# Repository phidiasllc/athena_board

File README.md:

The Athena Board is a 3-D printer controller board designed to interface with the Orange Pi Zero.

Note pin mappings can differ based upon the definition used by the firmware developer. The pin mapping shown in the spreadsheet is based on the mighty1284p definition; Sanguinololu uses different definitions.

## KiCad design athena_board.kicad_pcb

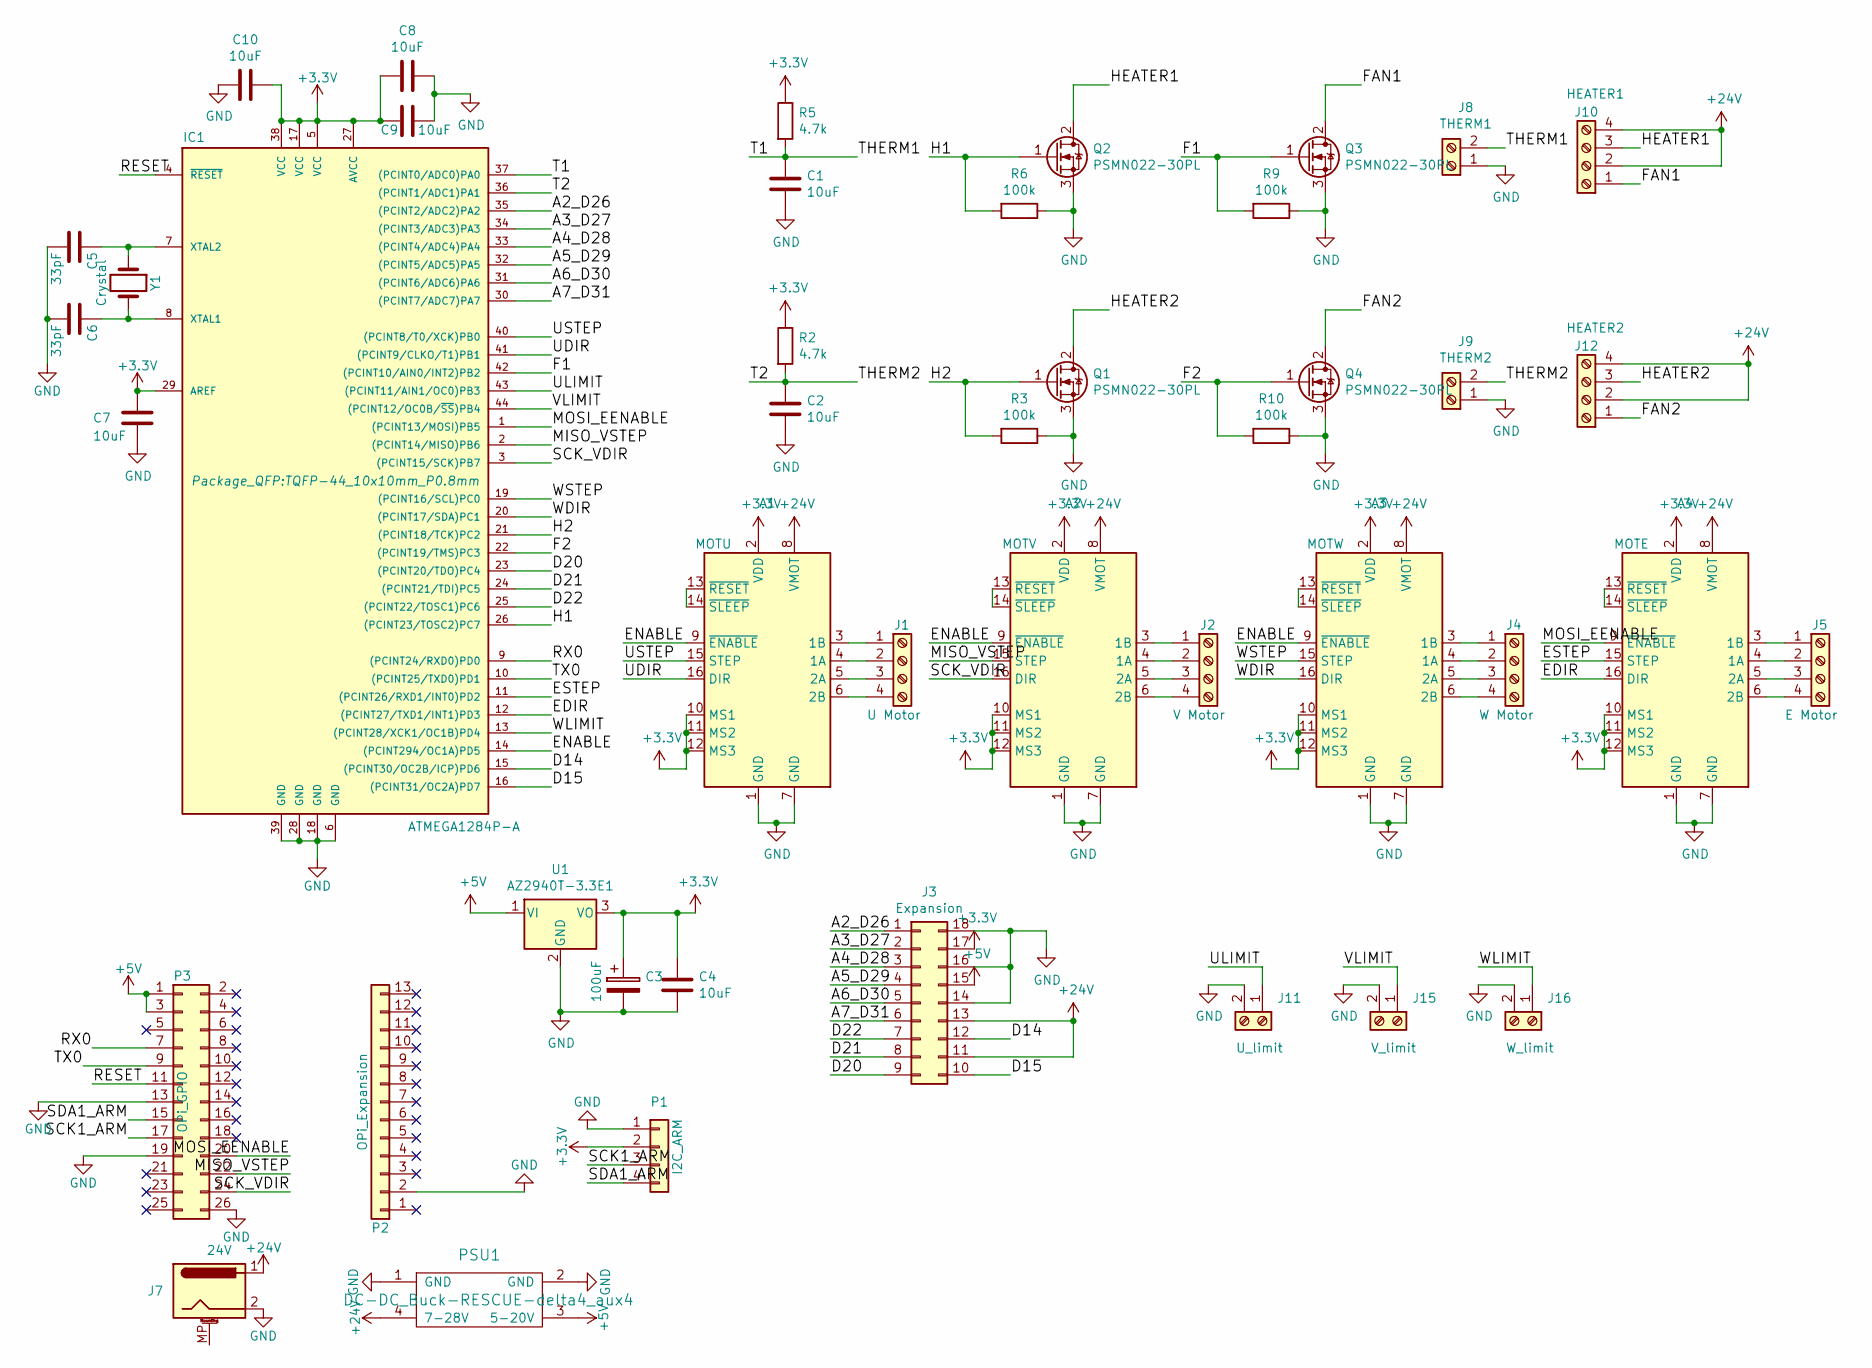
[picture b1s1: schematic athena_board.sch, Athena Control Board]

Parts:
A1: MOTU; Pololu_Breakout-16_15.2x20.3mm; digikey S7006-ND two required
A2: MOTV; Pololu_Breakout-16_15.2x20.3mm; digikey S7006-ND two required
A3: MOTW; Pololu_Breakout-16_15.2x20.3mm; digikey S7006-ND 2 required
A4: MOTE; Pololu_Breakout-16_15.2x20.3mm; digikey S7006-ND two required
C1, C2, C4, C7, C9, C10: 10uF; C_1206_3216Metric_Pad1.42x1.75mm_HandSolder; digikey 1276-1853-1-ND
C3: 100uF; C_1206_3216Metric_Pad1.42x1.75mm_HandSolder; digikey 478-12404-1-ND
C5, C6: 33pF; C_1206_3216Metric_Pad1.42x1.75mm_HandSolder; digikey 732-7873-1-ND
C8: 10uF; C_1206_3216Metric_Pad1.42x1.75mm_HandSolder
IC1: ATMEGA1284P-A; TQFP-44_10x10mm_P0.8mm; digikey ATMEGA1284P-AU-ND
J1: U Motor; SCREWTERMINAL-3.5MM-4; digikey 277-1860-ND
J2: V Motor; SCREWTERMINAL-3.5MM-4; digikey 277-1860-ND
J3: Expansion; PinSocket_2x09_P2.54mm_Vertical
J4: W Motor; SCREWTERMINAL-3.5MM-4; digikey 277-1860-ND
J5: E Motor; SCREWTERMINAL-3.5MM-4; digikey 277-1860-ND
J7: 24V; BarrelJack_Horizontal
J8: THERM1; SCREWTERMINAL-3.5MM-2; digikey 277-1721-ND
J9: THERM2; SCREWTERMINAL-3.5MM-2; digikey 277-1721-ND
J10: HEATER1; SCREWTERMINAL-5MM-4
J11: U_limit; SCREWTERMINAL-3.5MM-2; digikey 277-1721-ND
J12: HEATER2; SCREWTERMINAL-5MM-4
J15: V_limit; SCREWTERMINAL-3.5MM-2; digikey 277-1721-ND
J16: W_limit; SCREWTERMINAL-3.5MM-2; digikey 277-1721-ND
P1: I2C_ARM; PinHeader_1x04_P2.54mm_Vertical
P2: OPi_Expansion; PinHeader_1x13_P2.54mm_Vertical
P3: OPi_GPIO; PinHeader_2x13_P2.54mm_Vertical
PSU1: DC-DC_Buck-RESCUE-delta4_aux4; 7-28V
Q1, Q2, Q3, Q4: PSMN022-30PL; TO-220-3_Vertical; digikey 1727-5893-ND
R2, R5: 4.7k; R_1206_3216Metric; digikey A130181CT-ND
R3, R6, R9, R10: 100k; R_1206_3216Metric; digikey A129834CT-ND
U1: AZ2940T-3.3E1; TO-220-3_Vertical; digikey AZ2940T-3.3E1DI-ND
Y1: Crystal; Crystal_SMD_HC49-SD; digikey 535-9067-1-ND

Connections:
+3V3: A1.2 (VDD), A1.10 (MS1), A1.11 (MS2), A1.12 (MS3), A2.2 (VDD), A2.10 (MS1), A2.11 (MS2), A2.12 (MS3), A3.2 (VDD), A3.10 (MS1), A3.11 (MS2), A3.12 (MS3), A4.2 (VDD), A4.10 (MS1), A4.11 (MS2), A4.12 (MS3), C3.1, C4.1, C7.1, C8.2, C9.2, C10.2, IC1.5 (VCC), IC1.17 (VCC), IC1.27 (AVCC), IC1.29 (AREF), IC1.38 (VCC), J3.17, P1.2, R2.1, R5.1, U1.3 (VO)
+5V: J3.15, P3.1, P3.3, PSU1.3 (5-20V), U1.1 (VI)
+24V: A1.8 (VMOT), A2.8 (VMOT), A3.8 (VMOT), A4.8 (VMOT), J3.11, J3.13, J7.1, J10.2, J10.4, J12.2, J12.4, PSU1.4 (7-28V)
/A2_D26: IC1.35 ((PCINT2/ADC2)PA2), J3.1
/A3_D27: IC1.34 ((PCINT3/ADC3)PA3), J3.2
/A4_D28: IC1.33 ((PCINT4/ADC4)PA4), J3.3
/A5_D29: IC1.32 ((PCINT5/ADC5)PA5), J3.4
/A6_D30: IC1.31 ((PCINT6/ADC6)PA6), J3.5
/A7_D31: IC1.30 ((PCINT7/ADC7)PA7), J3.6
/D14: IC1.15 ((PCINT30/OC2B/ICP)PD6), J3.12
/D15: IC1.16 ((PCINT31/OC2A)PD7), J3.10
/D20: IC1.23 ((PCINT20/TDO)PC4), J3.9
/D21: IC1.24 ((PCINT21/TDI)PC5), J3.8
/D22: IC1.25 ((PCINT22/TOSC1)PC6), J3.7
/EDIR: A4.16 (DIR), IC1.12 ((PCINT27/TXD1/INT1)PD3)
/ENABLE: A1.9 (~ENABLE), A2.9 (~ENABLE), A3.9 (~ENABLE), IC1.14 ((PCINT294/OC1A)PD5)
/ESTEP: A4.15 (STEP), IC1.11 ((PCINT26/RXD1/INT0)PD2)
/F1: IC1.42 ((PCINT10/AIN0/INT2)PB2), Q3.1 (G), R9.2
/F2: IC1.22 ((PCINT19/TMS)PC3), Q4.1 (G), R10.2
/FAN1: J10.1, Q3.2 (D)
/FAN2: J12.1, Q4.2 (D)
/H1: IC1.26 ((PCINT23/TOSC2)PC7), Q2.1 (G), R6.2
/H2: IC1.21 ((PCINT18/TCK)PC2), Q1.1 (G), R3.2
/HEATER1: J10.3, Q2.2 (D)
/HEATER2: J12.3, Q1.2 (D)
/MISO_VSTEP: A2.15 (STEP), IC1.2 ((PCINT14/MISO)PB6), P3.22
/MOSI_EENABLE: A4.9 (~ENABLE), IC1.1 ((PCINT13/MOSI)PB5), P3.20
/RESET: IC1.4 (~RESET), P3.11
/RX0: IC1.9 ((PCINT24/RXD0)PD0), P3.7
/SCK1_ARM: P1.3, P3.17
/SCK_VDIR: A2.16 (DIR), IC1.3 ((PCINT15/SCK)PB7), P3.24
/SDA1_ARM: P1.4, P3.15
/T1: C1.1, IC1.37 ((PCINT0/ADC0)PA0), J8.2, R5.2
/T2: C2.1, IC1.36 ((PCINT1/ADC1)PA1), J9.2, R2.2
/TX0: IC1.10 ((PCINT25/TXD0)PD1), P3.9
/UDIR: A1.16 (DIR), IC1.41 ((PCINT9/CLKO/T1)PB1)
/ULIMIT: IC1.43 ((PCINT11/AIN1/OC0)PB3), J11.1
/USTEP: A1.15 (STEP), IC1.40 ((PCINT8/T0/XCK)PB0)
/VLIMIT: IC1.44 ((PCINT12/OC0B/~SS~)PB4), J15.1
/WDIR: A3.16 (DIR), IC1.20 ((PCINT17/SDA)PC1)
/WLIMIT: IC1.13 ((PCINT28/XCK1/OC1B)PD4), J16.1
/WSTEP: A3.15 (STEP), IC1.19 ((PCINT16/SCL)PC0)
GND: A1.1 (GND), A1.7 (GND), A2.1 (GND), A2.7 (GND), A3.1 (GND), A3.7 (GND), A4.1 (GND), A4.7 (GND), C1.2, C2.2, C3.2, C4.2, C5.2, C6.2, C7.2, C8.1, C9.1, C10.1, IC1.6 (GND), IC1.18 (GND), IC1.28 (GND), IC1.39 (GND), J3.14, J3.16, J3.18, J7.2, J8.1, J9.1, J11.2, J15.2, J16.2, P1.1, P2.2, P3.13, P3.19, P3.26, PSU1.1 (GND), PSU1.2 (GND), Q1.3 (S), Q2.3 (S), Q3.3 (S), Q4.3 (S), R3.1, R6.1, R9.1, R10.1, U1.2 (GND)
unnamed: A1.3 (1B), J1.1
unnamed: A1.4 (1A), J1.2
unnamed: A1.5 (2A), J1.3
unnamed: A1.6 (2B), J1.4
unnamed: A1.13 (~RESET), A1.14 (~SLEEP)
unnamed: A2.3 (1B), J2.1
unnamed: A2.4 (1A), J2.2
unnamed: A2.5 (2A), J2.3
unnamed: A2.6 (2B), J2.4
unnamed: A2.13 (~RESET), A2.14 (~SLEEP)
unnamed: A3.3 (1B), J4.1
unnamed: A3.4 (1A), J4.2
unnamed: A3.5 (2A), J4.3
unnamed: A3.6 (2B), J4.4
unnamed: A3.13 (~RESET), A3.14 (~SLEEP)
unnamed: A4.3 (1B), J5.1
unnamed: A4.4 (1A), J5.2
unnamed: A4.5 (2A), J5.3
unnamed: A4.6 (2B), J5.4
unnamed: A4.13 (~RESET), A4.14 (~SLEEP)
unnamed: C5.1, IC1.7 (XTAL2), Y1.1
unnamed: C6.1, IC1.8 (XTAL1), Y1.2

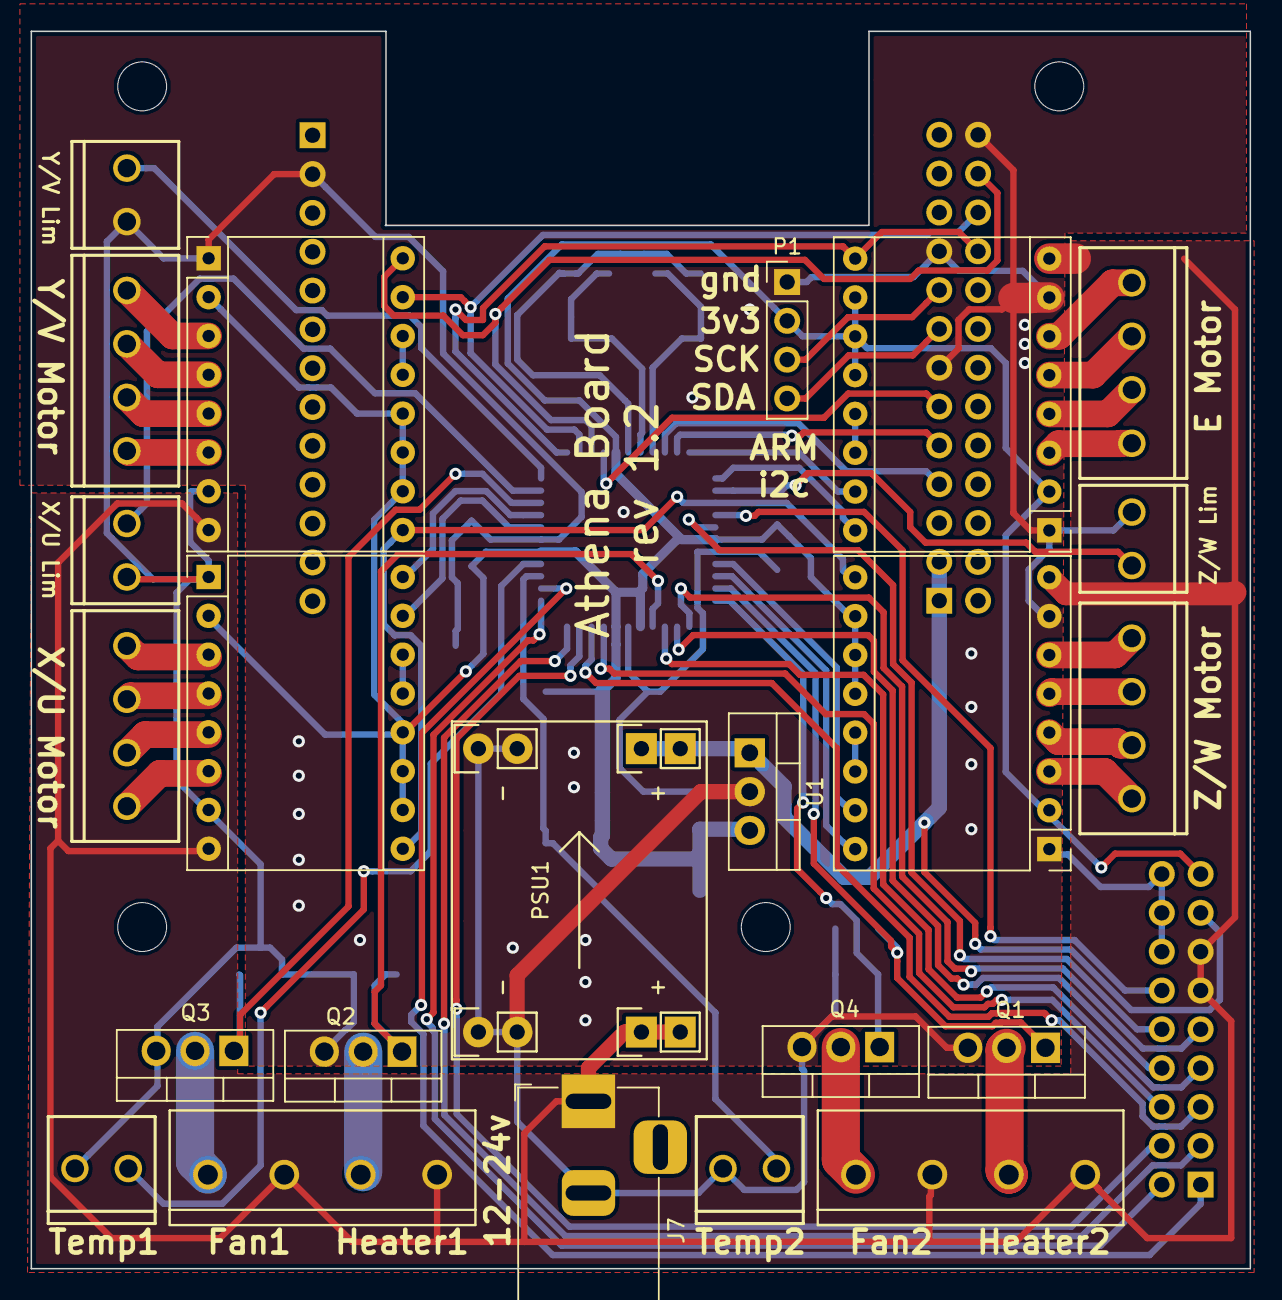
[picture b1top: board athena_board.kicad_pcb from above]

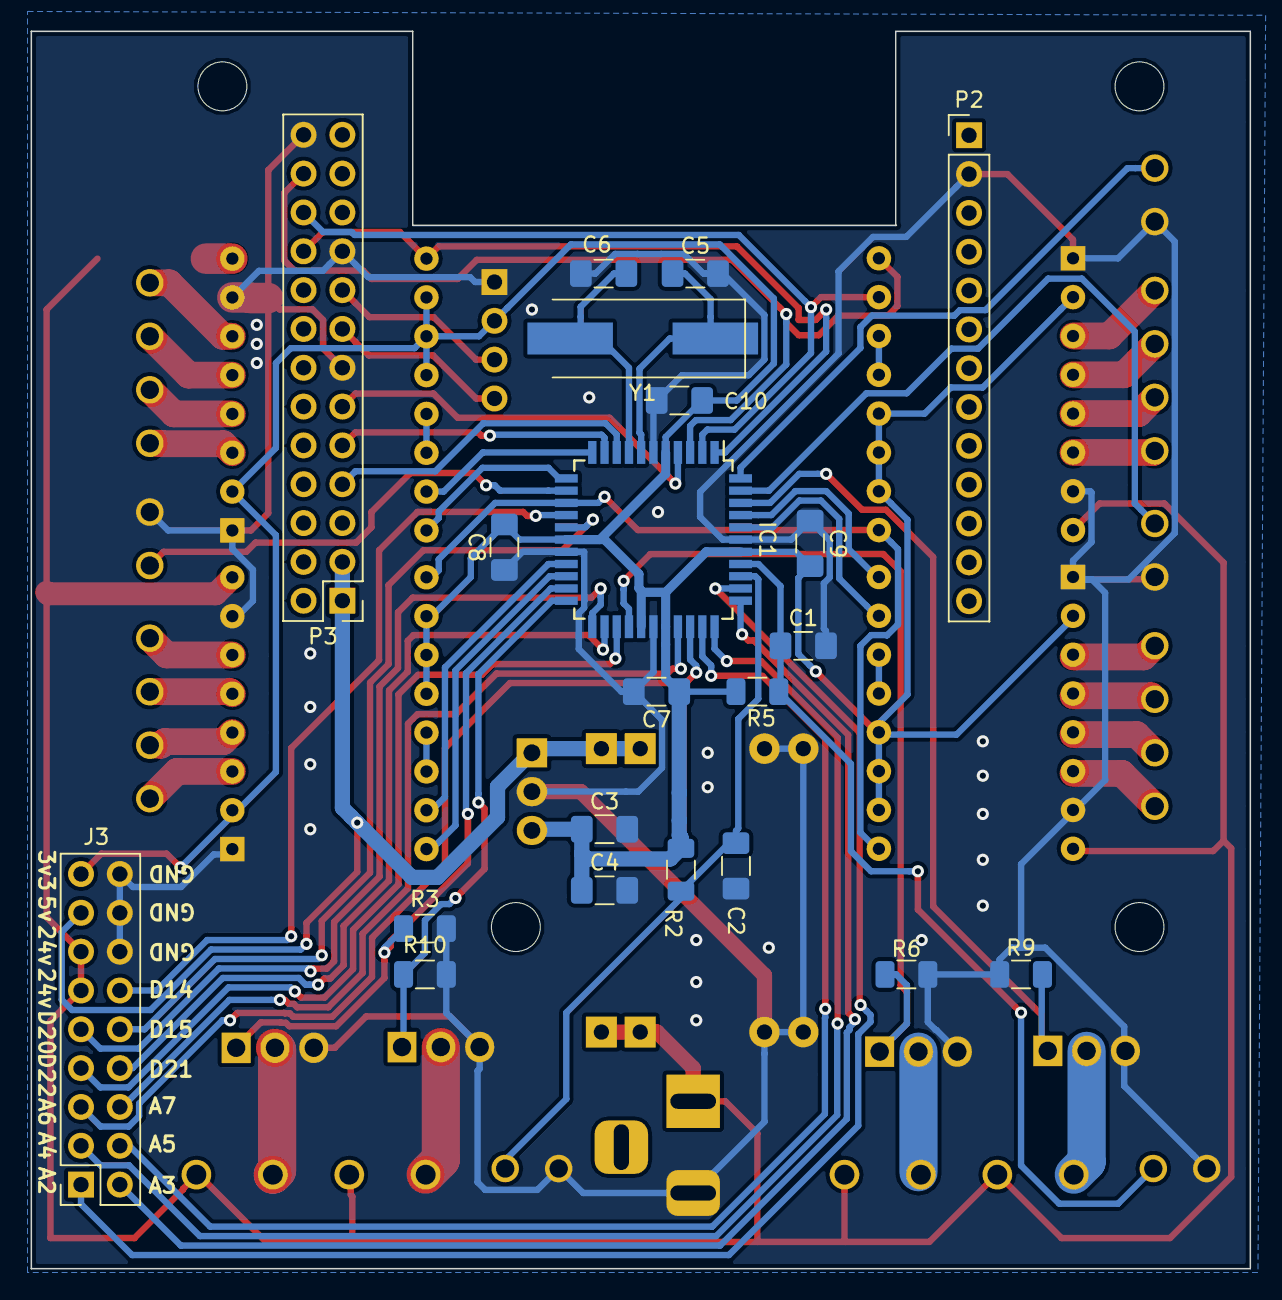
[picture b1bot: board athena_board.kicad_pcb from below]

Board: 2 copper layers, 79.8 x 81.0 mm, 44 parts (21 on the bottom side), 65 nets.
